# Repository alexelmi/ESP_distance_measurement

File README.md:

# Distance Measurement

A tiny handheld ultrasonic "distance radar" built on a WeMos D1 mini. The closer
you hold it to an object, the faster it blinks and beeps.

> This tiny project I made with my daughter. When she came to me asking for a
> little handheld which is peeping and blinking, I thought using an ultrasonic
> sensor could be fun.

So I sat down and designed the circuit and the PCB in KiCad:

| Schematic | PCB | 3D view |
|---|---|---|
|  |  |  |

The next day we put the components together and loaded the first test sketch onto
the WeMos D1 mini. (I have to admit I didn't test it before. 🙂)

## Features

- Ultrasonic distance measurement (~2 cm … 5 m) with an HC-SR04.
- LED + buzzer feedback that speeds up as the object gets closer; **solid** when
  very close and **silent** when nothing is in range.
- Distance also printed over `Serial` at 115200 baud.

## Hardware at a glance

| Function | WeMos label | ESP8266 GPIO |
|----------|-------------|--------------|
| Ultrasonic Trigger | D7 | GPIO13 |
| Ultrasonic Echo | D6 | GPIO12 |
| LED | D1 | GPIO5 |
| Buzzer (via transistor) | D3 | GPIO0 |

Full BOM, schematic, PCB and Gerbers are in [`Hardware/`](Hardware/). Pin mapping
verified against the KiCad netlist.

## Software

The code was built up from small test sketches, then combined into the final
firmware:

- **Ultrasonic test sketch** — [`Software/Test_UltraSonic_Simple`](Software/Test_UltraSonic_Simple) — prints the measured distance.
- **LED blink test sketch** — [`Software/Test_LED_Simple`](Software/Test_LED_Simple).
- **Buzzer beep test sketch** — [`Software/Test_Buzzer_Simple`](Software/Test_Buzzer_Simple).
- **Final firmware** — [`Software/Final_Software`](Software/Final_Software) — sensor + LED + buzzer combined.

### Quick start

1. Install the Arduino IDE and add ESP8266 board support
   (`https://arduino.esp8266.com/stable/package_esp8266com_index.json`).
2. Select board **LOLIN(WEMOS) D1 R2 & mini**.
3. Open `Software/Final_Software/Final_Software.ino`, upload, and open the Serial
   Monitor at **115200 baud**.

Step-by-step instructions are in the [full documentation](docs/DOCUMENTATION.md).

## Tests

The firmware's distance/beep logic is unit-tested on the host (no hardware
needed):

```sh
cd Software/Tests
c++ -std=c++11 -Wall -Wextra test_distance_logic.cpp -o test_distance_logic
./test_distance_logic
```

## Documentation

- 📘 [Full documentation](docs/DOCUMENTATION.md) — theory, hardware, firmware,
  build & flash, troubleshooting.
- 🛠️ [Work report](WORK_REPORT.md) — bugs fixed and improvements made.
- ✅ [Tests README](Software/Tests/README.md).

## License

See [LICENSE](LICENSE).

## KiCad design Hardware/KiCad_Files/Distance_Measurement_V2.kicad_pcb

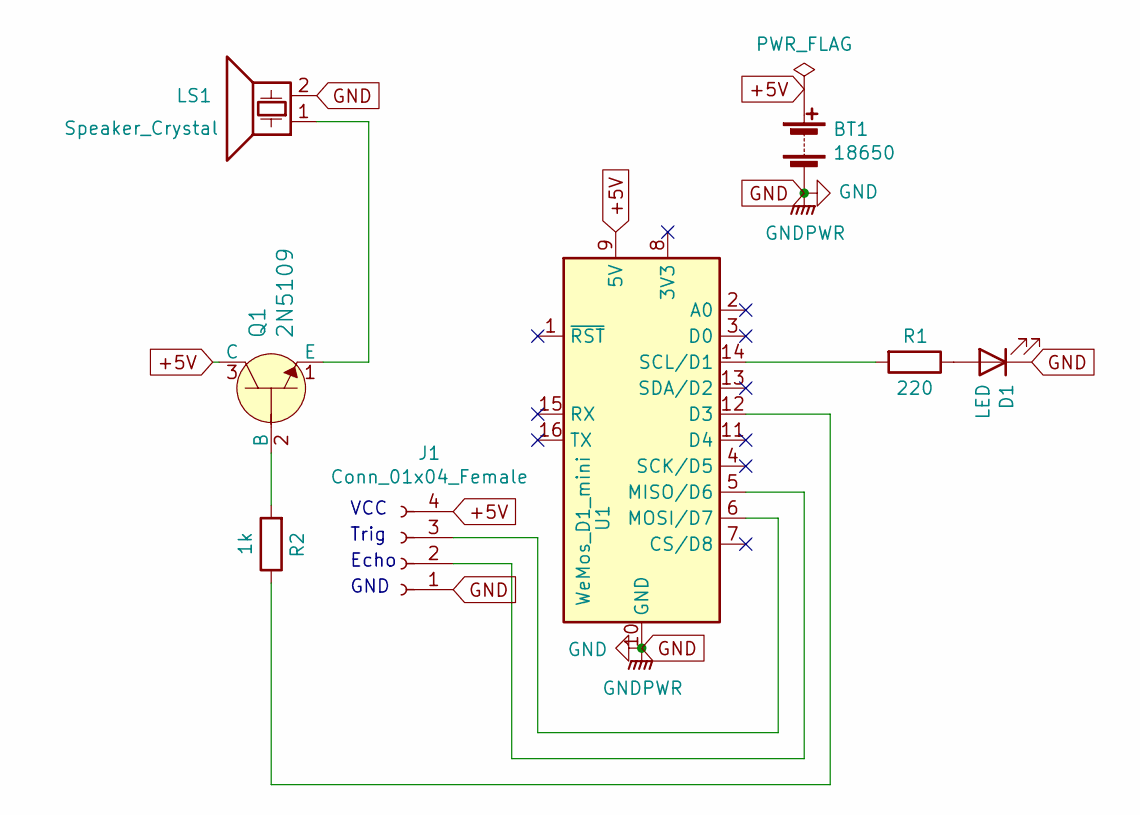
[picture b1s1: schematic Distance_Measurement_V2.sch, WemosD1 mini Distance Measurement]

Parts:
BT1: 18650; BatteryHolder_MPD_BH-18650-PC2
D1: LED; LED_D3.0mm
J1: Conn_01x04_Female; PinSocket_1x04_P2.54mm_Vertical
LS1: Speaker_Crystal; Piezo_Transducer_THT_PS1240P02BT
Q1: 2N5109; TO-92_Inline_Wide; MPN 2N5109; Digi-Key_PN 2N5109CS-ND
R1: 220; R_Axial_DIN0207_L6.3mm_D2.5mm_P10.16mm_Horizontal
R2: 1k; R_Axial_DIN0207_L6.3mm_D2.5mm_P10.16mm_Horizontal
U1: WeMos_D1_mini; WEMOS_D1_mini_light

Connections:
+5V: BT1.1 (+), J1.4, Q1.3 (C), U1.9 (5V)
GND: BT1.2 (-), D1.1 (K), J1.1, LS1.2, U1.10 (GND)
unnamed: D1.2 (A), R1.1
unnamed: J1.2, U1.5 (MISO/D6)
unnamed: J1.3, U1.6 (MOSI/D7)
unnamed: LS1.1, Q1.1 (E)
unnamed: Q1.2 (B), R2.2
unnamed: R1.2, U1.14 (SCL/D1)
unnamed: R2.1, U1.12 (D3)

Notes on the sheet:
VCC
Trig
Echo
GND

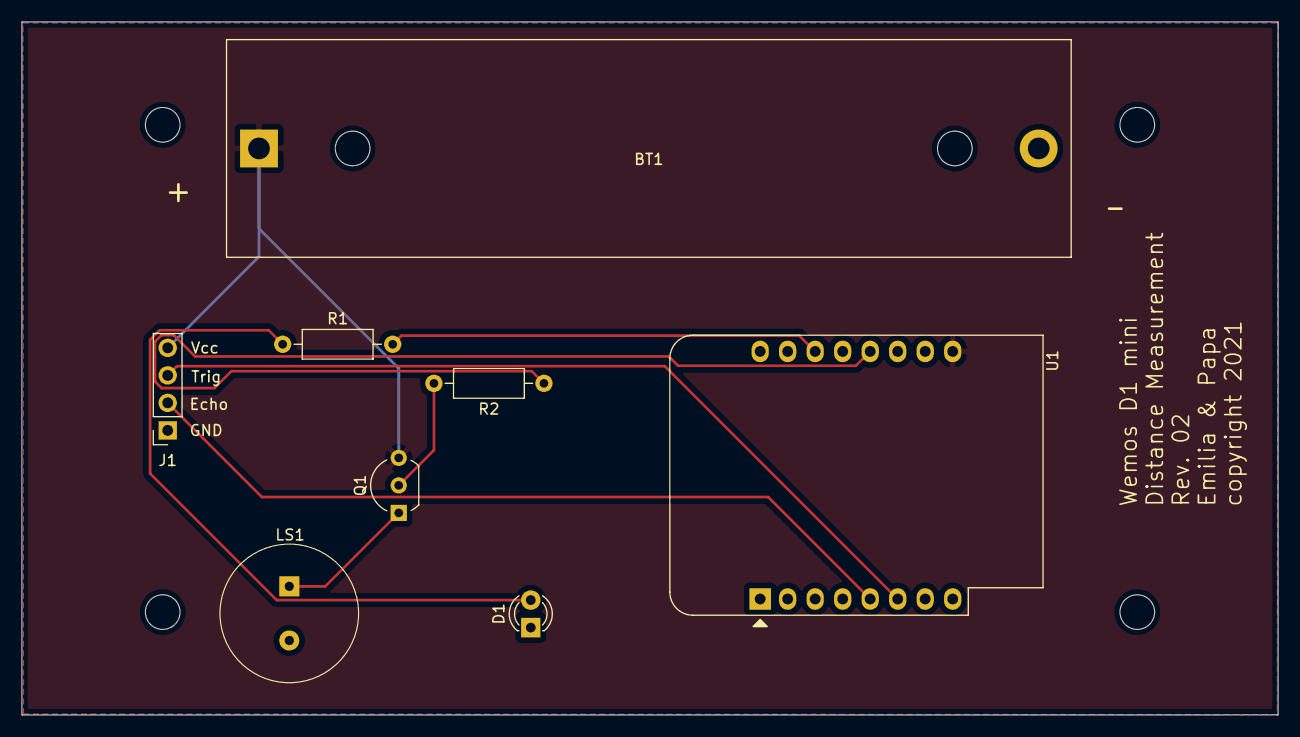
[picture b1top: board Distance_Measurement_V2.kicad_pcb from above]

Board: 2 copper layers, 116.0 x 64.0 mm, 8 parts (0 on the bottom side), 9 nets.

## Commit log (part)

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2021-05-05 updated layout with battery
2021-10-17 Update and KiCAD Files
2021-10-17 readme update
2021-10-19 .DS_Store banished!
2021-11-11 fixed a twisted GND/Vcc signal at PCB
2021-11-11 corrected failure on PCB
2021-11-11 update of Gerber
2021-11-27 added Version 2
    including a battery holder for 18650
2025-04-16 Create LICENSE
2025-04-16 changed GPIO ports

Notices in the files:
Hardware/KiCad_Files/Distance_Measurement_V2.kicad_pcb:
copyright 2021
